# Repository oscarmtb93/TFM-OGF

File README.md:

# TFM OGF
TFM para comprobar encripación ligera CAN

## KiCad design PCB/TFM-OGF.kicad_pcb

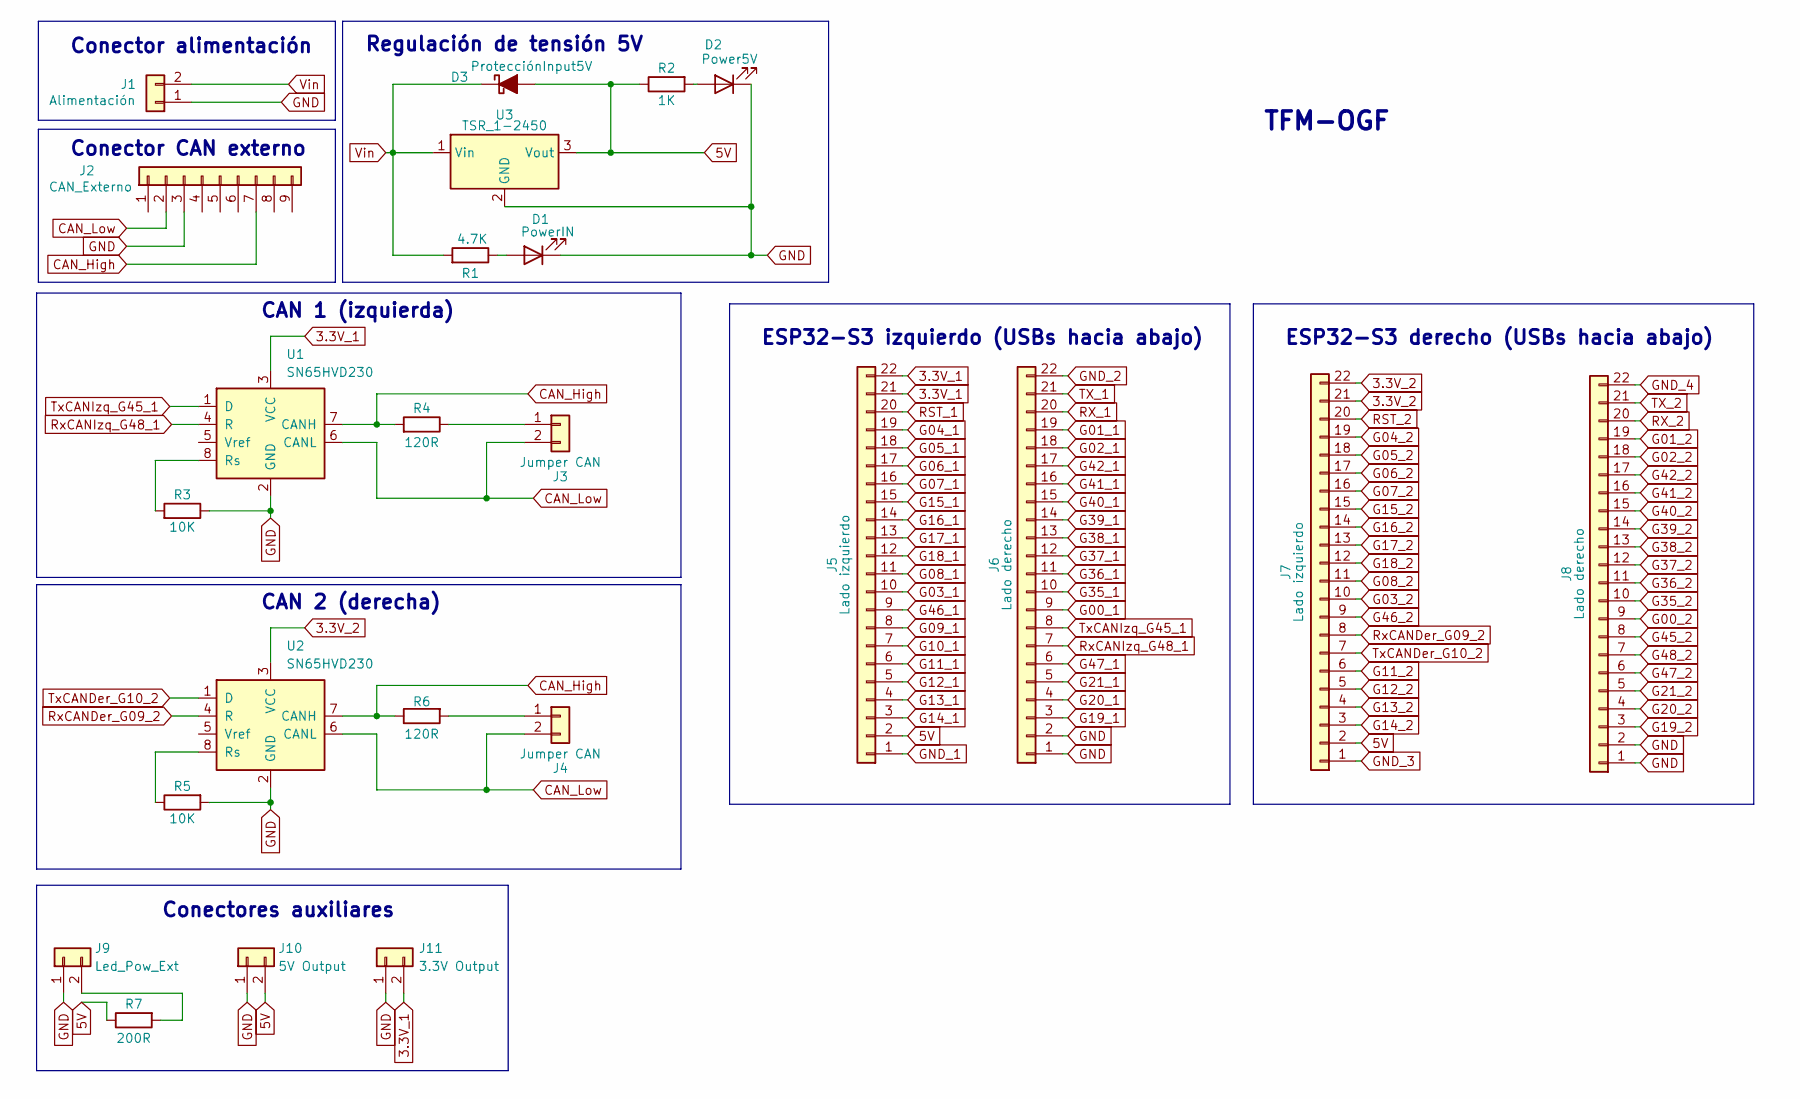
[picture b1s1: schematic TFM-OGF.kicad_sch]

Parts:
D1: PowerIN; LED_0805_2012Metric
D2: Power5V; LED_0805_2012Metric
D3: ProtecciónInput5V; D_SMA_Handsoldering
J1: Alimentación; AMASS_XT30UPB-M_1x02_P5.0mm_Vertical
J2: CAN_Externo; DSUB-9_Socket_Vertical_P2.77x2.84mm_MountingHoles
J3, J4: Jumper CAN; PinHeader_2x01_P2.54mm_Vertical
J5, J7: Lado izquierdo; PinSocket_1x22_P2.54mm_Vertical
J6, J8: Lado derecho; PinSocket_1x22_P2.54mm_Vertical
J9: Led_Pow_Ext; JST_XH_B2B-XH-A_1x02_P2.50mm_Vertical
J10: 5V Output; JST_XH_B2B-XH-A_1x02_P2.50mm_Vertical
J11: 3.3V Output; JST_XH_B2B-XH-A_1x02_P2.50mm_Vertical
R1: 4.7K; R_0603_1608Metric
R2: 1K; R_0603_1608Metric
R3, R5: 10K; R_0603_1608Metric
R4, R6: 120R; R_0603_1608Metric
R7: 200R; R_0603_1608Metric
U1, U2: SN65HVD230; SOIC-8_3.9x4.9mm_P1.27mm
U3: TSR_1-2450; Converter_DCDC_TRACO_TSR-1_THT

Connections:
3.3V_1: J5.21, J5.22, J11.2, U1.3 (VCC)
3.3V_2: J7.21, J7.22, U2.3 (VCC)
5V: D3.2 (A), J5.2, J7.2, J10.2, R2.1, R7.1, U3.3 (Vout)
CAN_High: J2.7, R4.2, R6.1, U1.7 (CANH), U2.7 (CANH)
CAN_Low: J2.2, J3.2, J4.2, U1.6 (CANL), U2.6 (CANL)
G00_1: J6.9
G00_2: J8.9
G01_1: J6.19
G01_2: J8.19
G02_1: J6.18
G02_2: J8.18
G03_1: J5.10
G03_2: J7.10
G04_1: J5.19
G04_2: J7.19
G05_1: J5.18
G05_2: J7.18
G06_1: J5.17
G06_2: J7.17
G07_1: J5.16
G07_2: J7.16
G08_1: J5.11
G08_2: J7.11
G09_1: J5.8
G10_1: J5.7
G11_1: J5.6
G11_2: J7.6
G12_1: J5.5
G12_2: J7.5
G13_1: J5.4
G13_2: J7.4
G14_1: J5.3
G14_2: J7.3
G15_1: J5.15
G15_2: J7.15
G16_1: J5.14
G16_2: J7.14
G17_1: J5.13
G17_2: J7.13
G18_1: J5.12
G18_2: J7.12
G19_1: J6.3
G19_2: J8.3
G20_1: J6.4
G20_2: J8.4
G21_1: J6.5
G21_2: J8.5
G35_1: J6.10
G35_2: J8.10
G36_1: J6.11
G36_2: J8.11
G37_1: J6.12
G37_2: J8.12
G38_1: J6.13
G38_2: J8.13
G39_1: J6.14
G39_2: J8.14
G40_1: J6.15
G40_2: J8.15
G41_1: J6.16
G41_2: J8.16
G42_1: J6.17
G42_2: J8.17
G45_2: J8.8
G46_1: J5.9
G46_2: J7.9
G47_1: J6.6
G47_2: J8.6
G48_2: J8.7
GND: D1.1 (K), D2.1 (K), J1.1, J2.3, J6.1, J6.2, J8.1, J8.2, J9.1, J10.1, J11.1, R3.1, R5.2, U1.2 (GND), U2.2 (GND), U3.2 (GND)
GND_1: J5.1
GND_2: J6.22
GND_3: J7.1
GND_4: J8.22
unnamed: D1.2 (A), R1.1
unnamed: D2.2 (A), R2.2
unnamed: J3.1, R4.1
unnamed: J4.1, R6.2
unnamed: J9.2, R7.2
unnamed: R3.2, U1.8 (Rs)
unnamed: R5.1, U2.8 (Rs)
RST_1: J5.20
RST_2: J7.20
RX_1: J6.20
RX_2: J8.20
RxCANDer_G09_2: J7.8, U2.4 (R)
RxCANIzq_G48_1: J6.7, U1.4 (R)
TX_1: J6.21
TX_2: J8.21
TxCANDer_G10_2: J7.7, U2.1 (D)
TxCANIzq_G45_1: J6.8, U1.1 (D)
Vin: D3.1 (K), J1.2, R1.2, U3.1 (Vin)

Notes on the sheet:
CAN 1 (izquierda)
Conectores auxiliares
Conector alimentación
Conector CAN externo
ESP32-S3 derecho (USBs hacia abajo)
TFM-OGF
Regulación de tensión 5V
CAN 2 (derecha)
ESP32-S3 izquierdo (USBs hacia abajo)

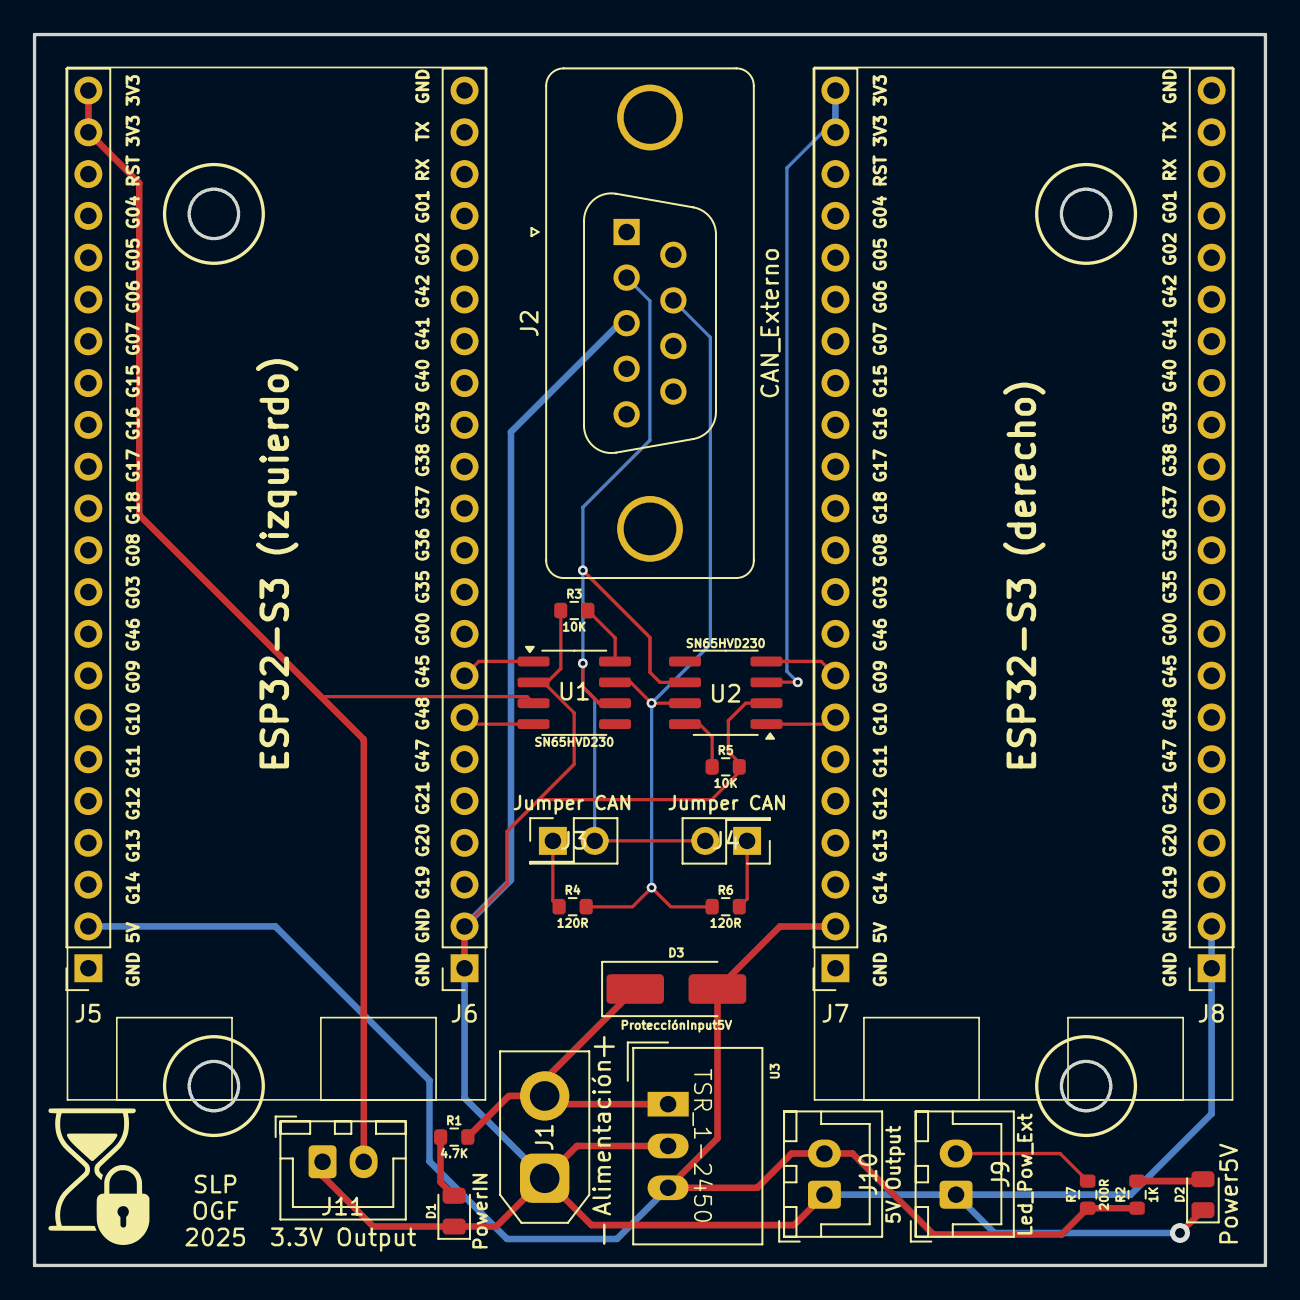
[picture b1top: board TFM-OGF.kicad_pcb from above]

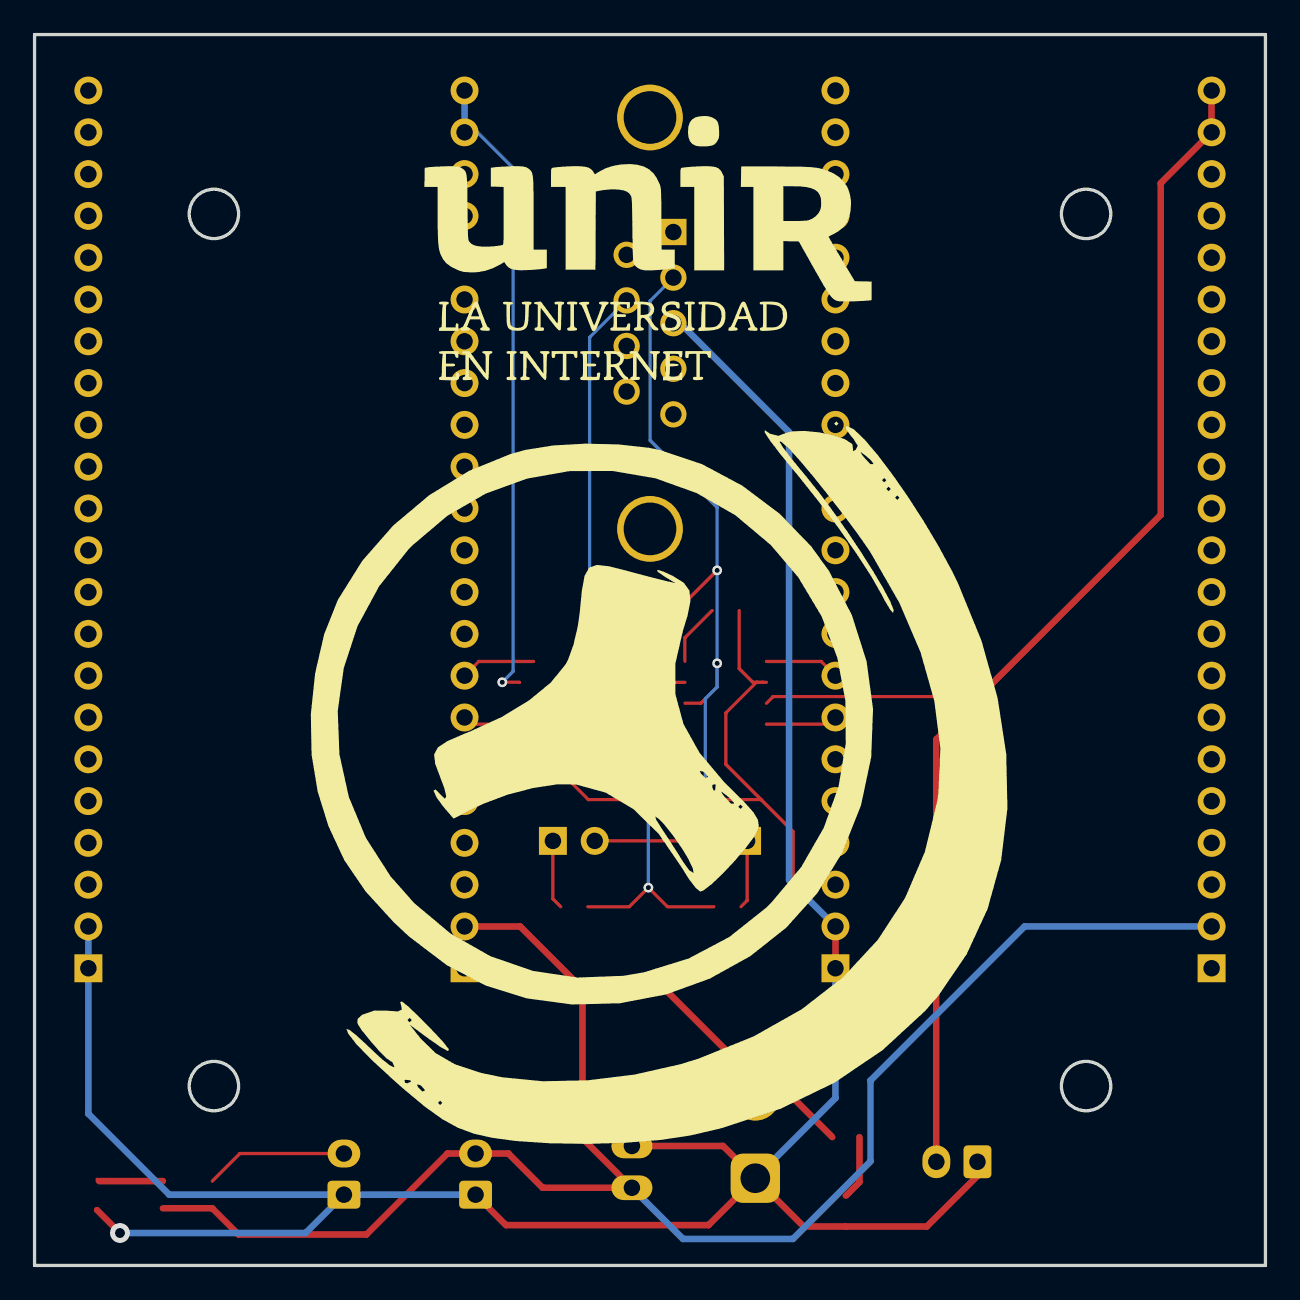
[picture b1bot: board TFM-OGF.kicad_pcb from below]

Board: 2 copper layers, 74.8 x 74.8 mm, 27 parts (2 on the bottom side), 18 nets.

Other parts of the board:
G1, G2, G3: LOGO

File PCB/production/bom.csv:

Designator,Footprint,Quantity,Value,LCSC Part #
D1,0805,1,PowerIN,C2297
D2,0805,1,Power5V,C2297
D3,D_SMA_Handsoldering,1,ProtecciónInput5V,C8678
J1,AMASS_XT30UPB-M_1x02_P5.0mm_Vertical,1,Alimentación,C428721
J10,JST_XH_B2B-XH-A_1x02_P2.50mm_Vertical,1,5V Output,C158012
J11,JST_XH_B2B-XH-A_1x02_P2.50mm_Vertical,1,3.3V Output,C158012
J2,DSUB-9_Socket_Vertical_P2.77x2.84mm_MountingHoles,1,CAN_Externo,C183530
"J3, J4",PinHeader_2x01_P2.54mm_Vertical,2,Jumper CAN,C492401
"J5, J7",PinSocket_1x22_P2.54mm_Vertical,2,Lado izquierdo,C7499337
"J6, J8",PinSocket_1x22_P2.54mm_Vertical,2,Lado derecho,C7499337
J9,JST_XH_B2B-XH-A_1x02_P2.50mm_Vertical,1,Led_Pow_Ext,C158012
R1,0603,1,4.7K,C23162
R2,0603,1,1K,C21190
"R3, R5",0603,2,10K,C25804
"R4, R6",0603,2,120R,C22787
R7,0603,1,200R,C8218
"U1, U2",SOIC-8_3.9x4.9mm_P1.27mm,2,SN65HVD230,C12084

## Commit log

2025-05-02 Inicializo proyectos de VSCode y KiCad
2025-05-02 Inicio esquemático
2025-05-08 Añado huella del Molex 3 pines
2025-05-11 Finalizo esquemático, usaré medidas y caja de BrakeCAN
2025-05-11 Primera versión de colocar los componentes
2025-05-11 Corrijo orientación de algunas resistencias
2025-05-11 Completo placa
2025-05-13 Amplío la placa 0.8mm a la derecha
2025-05-27 Centro los componentes del medio al haber aumentado 0,8mm a la derecha
2025-06-21 Cambio símbolo y huella TSR1 para usar los de KiCad, regenero ficheros de producción
2025-06-25 Elijo el ESP32 correcto y añado el código de carga máxima
2025-06-25 Inicio código de prueba para recibir y enviar mensajes CAN
2025-07-15 Realizo la prueba del envío de datos sin cifrar
2025-07-15 Cada ESP envía en un ID y recibe en otro
2025-07-15 Añado el cifrado AES-128 y el código de generación de claves
2025-07-15 Añado cifrado AES-256 y elimino referencias a AES-192
2025-07-16 Muevo el inicializar y liberar cifrador y hago 101 iteraciones sin cifrar y elimino la primera
2025-07-16 Todas las pruebas hacen 101 iteraciones pero no almacenan el tiempo de la primera
2025-07-16 Se realiza firma con SHA-1 y se profesionaliza la impresión por Serial
2025-07-31 Se realiza la firma MD5
2025-08-17 Se realiza la firma SHA-224
2025-08-17 Se realiza la firma SHA-256
2025-08-17 Se realiza la firma SHA-384
2025-08-17 Se realiza la firma SHA-512
2025-08-17 Se realiza el cifrado RSA-2048
2025-08-17 Almaceno todas las medias de los resultados en ms en vez de us
2025-08-17 Muevo el liberar los contextos fuera de la ejecución cronometrada
2025-08-17 Se realiza el cifrado RSA-3072
2025-08-17 Se realiza el cifrado RSA-4096
2025-08-19 Se corrige error de impresión por pantalla
